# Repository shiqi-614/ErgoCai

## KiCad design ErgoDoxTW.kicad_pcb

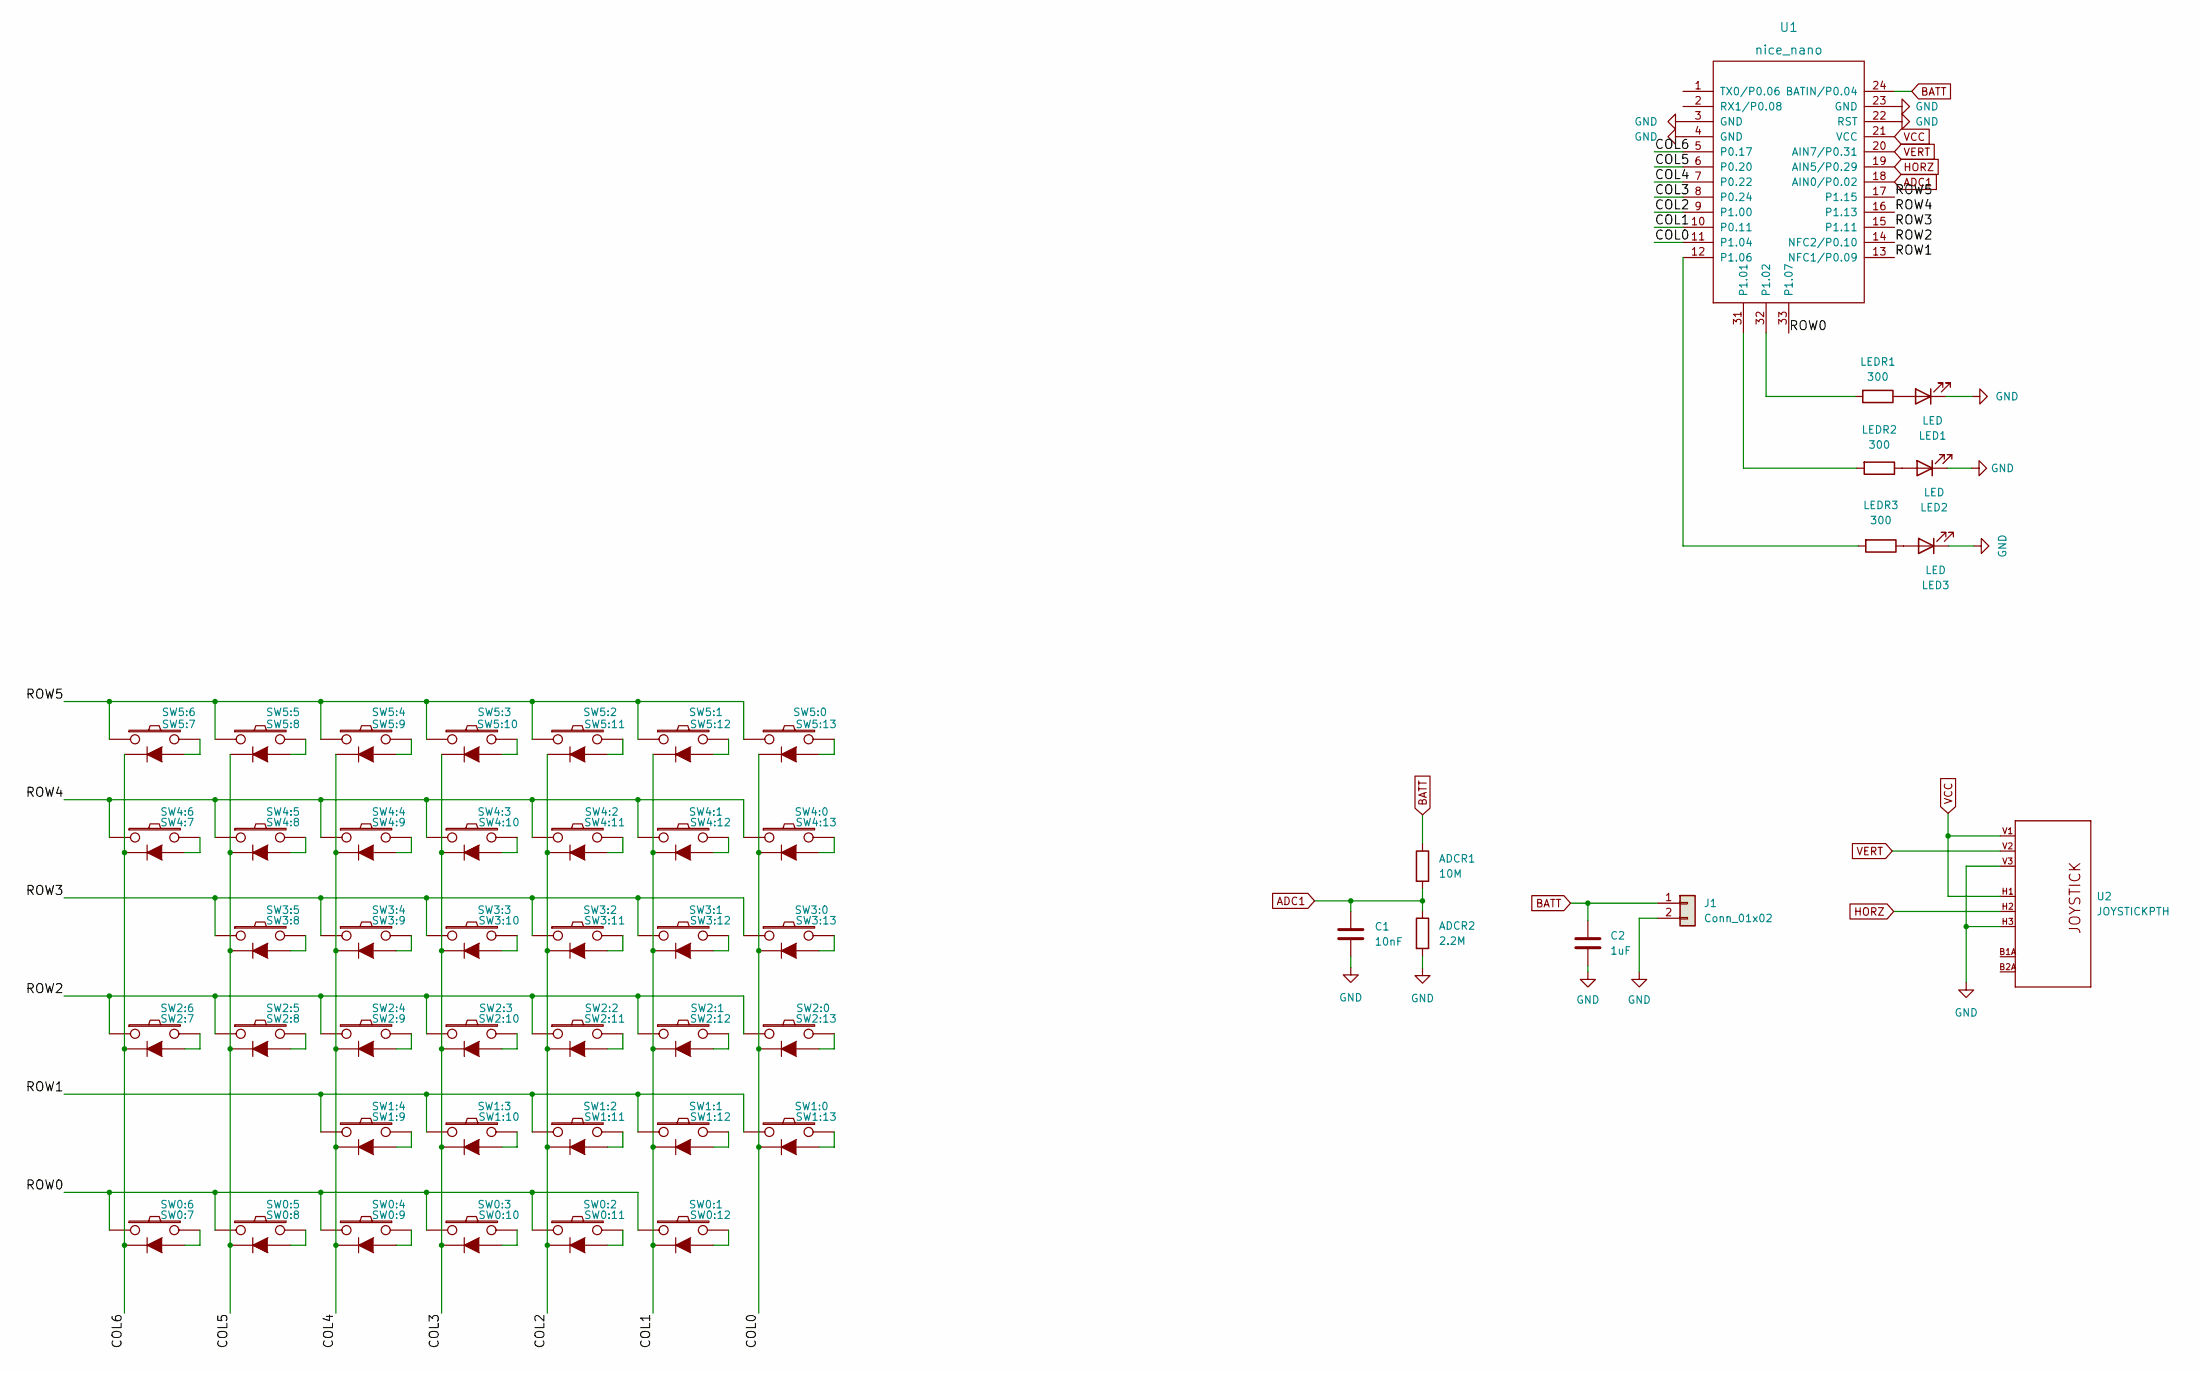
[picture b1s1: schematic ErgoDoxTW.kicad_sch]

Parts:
ADCR1: 10M; R_0805_2012Metric
ADCR2: 2.2M; R_0805_2012Metric
C1: 10nF; C_0805_2012Metric
C2: 1uF; C_0805_2012Metric
J1: Conn_01x02; PinHeader_1x02_P2.54mm_Vertical
LED1, LED2, LED3: LED; LED_0805_2012Metric
LEDR1, LEDR2, LEDR3: 300; R_0805_2012Metric
SW0:7: SW0:6; Kailh_socket_diode_smd
SW0:8: SW0:5; Kailh_socket_diode_smd
SW0:9: SW0:4; Kailh_socket_diode_smd
SW0:10: SW0:3; Kailh_socket_diode_smd
SW0:11: SW0:2; Kailh_socket_diode_smd
SW0:12: SW0:1; Kailh_socket_diode_smd
SW1:9: SW1:4; Kailh_socket_diode_smd
SW1:10: SW1:3; Kailh_socket_diode_smd
SW1:11: SW1:2; Kailh_socket_diode_smd
SW1:12: SW1:1; Kailh_socket_diode_smd
SW1:13: SW1:0; Kailh_socket_diode_smd
SW2:7: SW2:6; Kailh_socket_diode_smd
SW2:8: SW2:5; Kailh_socket_diode_smd
SW2:9: SW2:4; Kailh_socket_diode_smd
SW2:10: SW2:3; Kailh_socket_diode_smd
SW2:11: SW2:2; Kailh_socket_diode_smd
SW2:12: SW2:1; Kailh_socket_diode_smd
SW2:13: SW2:0; Kailh_socket_diode_smd
SW3:8: SW3:5; Kailh_socket_diode_smd
SW3:9: SW3:4; Kailh_socket_diode_smd
SW3:10: SW3:3; Kailh_socket_diode_smd
SW3:11: SW3:2; Kailh_socket_diode_smd
SW3:12: SW3:1; Kailh_socket_diode_smd
SW3:13: SW3:0; Kailh_socket_diode_smd
SW4:7: SW4:6; Kailh_socket_diode_smd
SW4:8: SW4:5; Kailh_socket_diode_smd
SW4:9: SW4:4; Kailh_socket_diode_smd
SW4:10: SW4:3; Kailh_socket_diode_smd
SW4:11: SW4:2; Kailh_socket_diode_smd
SW4:12: SW4:1; Kailh_socket_diode_smd
SW4:13: SW4:0; Kailh_socket_diode_smd
SW5:7: SW5:6; Kailh_socket_diode_smd
SW5:8: SW5:5; Kailh_socket_diode_smd
SW5:9: SW5:4; Kailh_socket_diode_smd
SW5:10: SW5:3; Kailh_socket_diode_smd
SW5:11: SW5:2; Kailh_socket_diode_smd
SW5:12: SW5:1; Kailh_socket_diode_smd
SW5:13: SW5:0; Kailh_socket_diode_smd
U1: nice_nano
U2: JOYSTICKPTH; JOYSTICK

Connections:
/COL0: SW1:13.4 (K), SW2:13.4 (K), SW3:13.4 (K), SW4:13.4 (K), SW5:13.4 (K), U1.11 (P1.04)
/COL1: SW0:12.4 (K), SW1:12.4 (K), SW2:12.4 (K), SW3:12.4 (K), SW4:12.4 (K), SW5:12.4 (K), U1.10 (P0.11)
/COL2: SW0:11.4 (K), SW1:11.4 (K), SW2:11.4 (K), SW3:11.4 (K), SW4:11.4 (K), SW5:11.4 (K), U1.9 (P1.00)
/COL3: SW0:10.4 (K), SW1:10.4 (K), SW2:10.4 (K), SW3:10.4 (K), SW4:10.4 (K), SW5:10.4 (K), U1.8 (P0.24)
/COL4: SW0:9.4 (K), SW1:9.4 (K), SW2:9.4 (K), SW3:9.4 (K), SW4:9.4 (K), SW5:9.4 (K), U1.7 (P0.22)
/COL5: SW0:8.4 (K), SW2:8.4 (K), SW3:8.4 (K), SW4:8.4 (K), SW5:8.4 (K), U1.6 (P0.20)
/COL6: SW0:7.4 (K), SW2:7.4 (K), SW4:7.4 (K), SW5:7.4 (K), U1.5 (P0.17)
/ROW0: SW0:7.1, SW0:8.1, SW0:9.1, SW0:10.1, SW0:11.1, SW0:12.1, U1.33 (P1.07)
/ROW1: SW1:9.1, SW1:10.1, SW1:11.1, SW1:12.1, SW1:13.1, U1.13 (NFC1/P0.09)
/ROW2: SW2:7.1, SW2:8.1, SW2:9.1, SW2:10.1, SW2:11.1, SW2:12.1, SW2:13.1, U1.14 (NFC2/P0.10)
/ROW3: SW3:8.1, SW3:9.1, SW3:10.1, SW3:11.1, SW3:12.1, SW3:13.1, U1.15 (P1.11)
/ROW4: SW4:7.1, SW4:8.1, SW4:9.1, SW4:10.1, SW4:11.1, SW4:12.1, SW4:13.1, U1.16 (P1.13)
/ROW5: SW5:7.1, SW5:8.1, SW5:9.1, SW5:10.1, SW5:11.1, SW5:12.1, SW5:13.1, U1.17 (P1.15)
ADC1: ADCR1.2, ADCR2.1, C1.1, U1.18 (AIN0/P0.02)
BATT: ADCR1.1, C2.1, J1.1, U1.24 (BATIN/P0.04)
GND: ADCR2.2, C1.2, C2.2, J1.2, LED1.1 (K), LED2.1 (K), LED3.1 (K), U1.3 (GND), U1.4 (GND), U1.22 (RST), U1.23 (GND), U2.H3 (H-), U2.V3 (V-)
HORZ: U1.19 (AIN5/P0.29), U2.H2 (H)
unnamed: LED1.2 (A), LEDR1.1
unnamed: LED2.2 (A), LEDR2.1
unnamed: LED3.2 (A), LEDR3.1
unnamed: LEDR1.2, U1.32 (P1.02)
unnamed: LEDR2.2, U1.31 (P1.01)
unnamed: LEDR3.2, U1.12 (P1.06)
unnamed: SW0:7.2, SW0:7.3 (A)
unnamed: SW0:8.2, SW0:8.3 (A)
unnamed: SW0:9.2, SW0:9.3 (A)
unnamed: SW0:10.2, SW0:10.3 (A)
unnamed: SW0:11.2, SW0:11.3 (A)
unnamed: SW0:12.2, SW0:12.3 (A)
unnamed: SW1:9.2, SW1:9.3 (A)
unnamed: SW1:10.2, SW1:10.3 (A)
unnamed: SW1:11.2, SW1:11.3 (A)
unnamed: SW1:12.2, SW1:12.3 (A)
unnamed: SW1:13.2, SW1:13.3 (A)
unnamed: SW2:7.2, SW2:7.3 (A)
unnamed: SW2:8.2, SW2:8.3 (A)
unnamed: SW2:9.2, SW2:9.3 (A)
unnamed: SW2:10.2, SW2:10.3 (A)
unnamed: SW2:11.2, SW2:11.3 (A)
unnamed: SW2:12.2, SW2:12.3 (A)
unnamed: SW2:13.2, SW2:13.3 (A)
unnamed: SW3:8.2, SW3:8.3 (A)
unnamed: SW3:9.2, SW3:9.3 (A)
unnamed: SW3:10.2, SW3:10.3 (A)
unnamed: SW3:11.2, SW3:11.3 (A)
unnamed: SW3:12.2, SW3:12.3 (A)
unnamed: SW3:13.2, SW3:13.3 (A)
unnamed: SW4:7.2, SW4:7.3 (A)
unnamed: SW4:8.2, SW4:8.3 (A)
unnamed: SW4:9.2, SW4:9.3 (A)
unnamed: SW4:10.2, SW4:10.3 (A)
unnamed: SW4:11.2, SW4:11.3 (A)
unnamed: SW4:12.2, SW4:12.3 (A)
unnamed: SW4:13.2, SW4:13.3 (A)
unnamed: SW5:7.2, SW5:7.3 (A)
unnamed: SW5:8.2, SW5:8.3 (A)
unnamed: SW5:9.2, SW5:9.3 (A)
unnamed: SW5:10.2, SW5:10.3 (A)
unnamed: SW5:11.2, SW5:11.3 (A)
unnamed: SW5:12.2, SW5:12.3 (A)
unnamed: SW5:13.2, SW5:13.3 (A)
VCC: U1.21 (VCC), U2.H1 (H+), U2.V1 (V+)
VERT: U1.20 (AIN7/P0.31), U2.V2 (V)

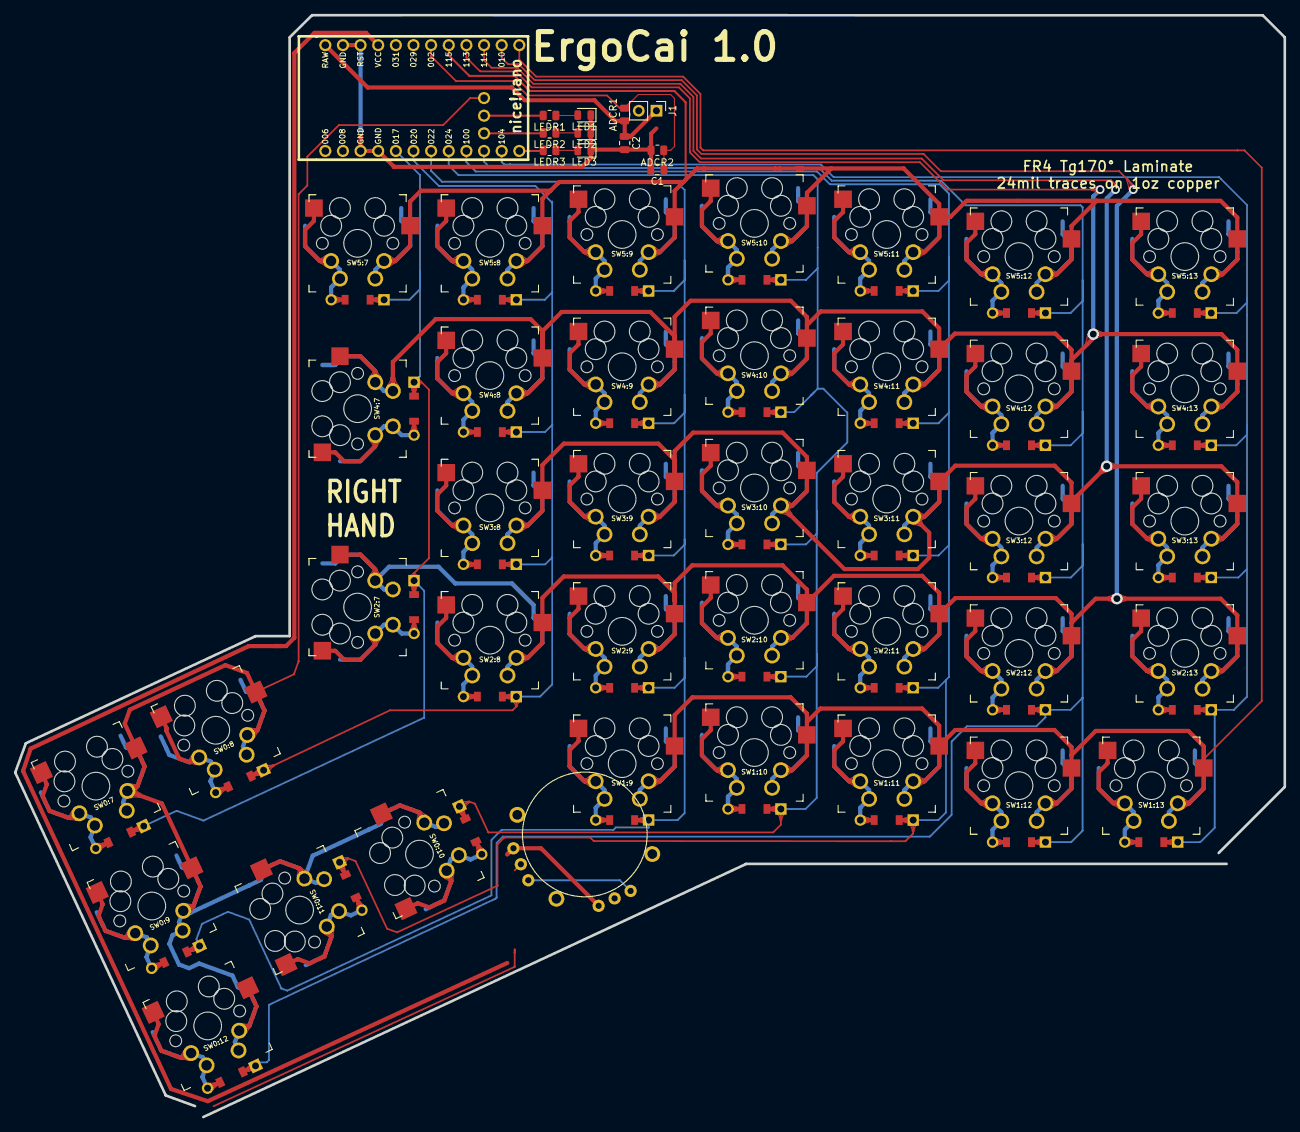
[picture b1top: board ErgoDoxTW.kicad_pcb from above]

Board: 2 copper layers, 182.8 x 158.7 mm, 51 parts (0 on the bottom side), 63 nets.
